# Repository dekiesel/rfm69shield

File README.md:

# rfm69shield
# rfm69shield
TODO: The extra GND isn't connected to any GND line

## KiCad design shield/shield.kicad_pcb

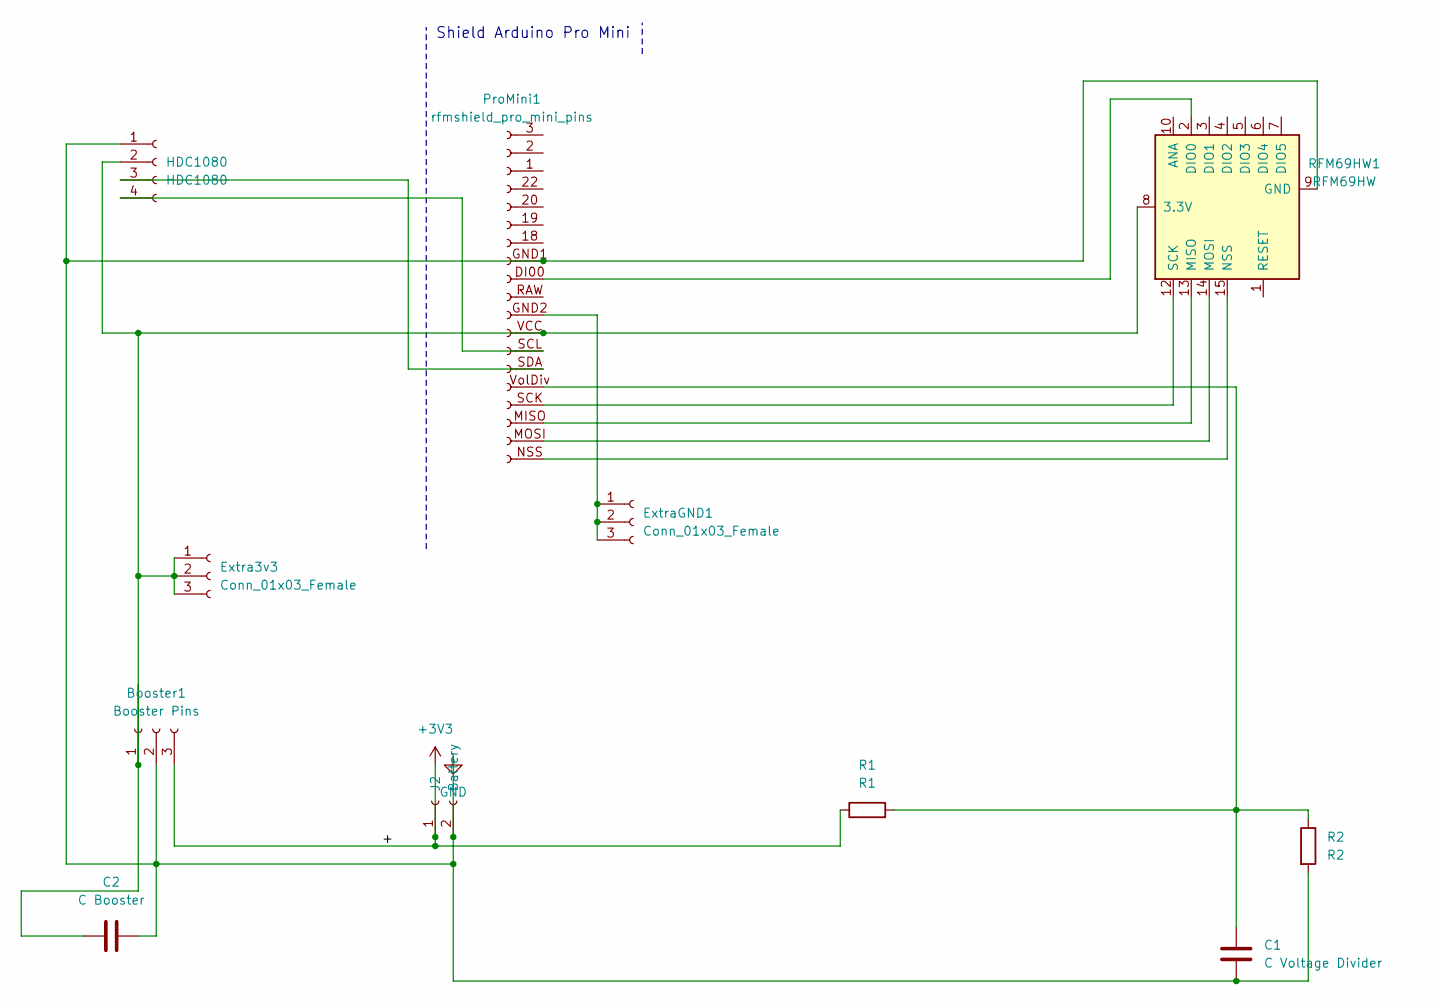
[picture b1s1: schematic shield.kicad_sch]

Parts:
Booster1: Booster Pins; PinHeader_1x03_P2.54mm_Vertical
C1: C Voltage Divider; CP_Radial_D6.3mm_P2.50mm
C2: C Booster; CP_Radial_D6.3mm_P2.50mm
Extra3v3: Conn_01x03_Female; PinHeader_1x03_P2.54mm_Vertical
ExtraGND1: Conn_01x03_Female; PinHeader_1x03_P2.54mm_Vertical
HDC1080: HDC1080; PinHeader_1x04_P2.54mm_Vertical
J2: Battery; PinHeader_1x02_P2.54mm_Vertical
ProMini1: rfmshield_pro_mini_pins; pro_mini_rfmshield
R1: R1; R_Axial_DIN0207_L6.3mm_D2.5mm_P10.16mm_Horizontal
R2: R2; R_Axial_DIN0207_L6.3mm_D2.5mm_P10.16mm_Horizontal
RFM69HW1: RFM69HW; HOPERF_RFM69HW

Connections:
+3V3: Booster1.3, J2.1, R1.1
GND: Booster1.2, C1.2, C2.2, HDC1080.1, J2.2, ProMini1.GND1, R2.2, RFM69HW1.9 (GND), RFM69HW1.11 (GND)
unnamed: Booster1.1, C2.1, Extra3v3.1, Extra3v3.2, Extra3v3.3, HDC1080.2, ProMini1.VCC, RFM69HW1.8 (3.3V)
unnamed: C1.1, ProMini1.VolDiv, R1.2, R2.1
unnamed: ExtraGND1.1, ExtraGND1.2, ExtraGND1.3, ProMini1.GND2
unnamed: HDC1080.3, ProMini1.SDA
unnamed: HDC1080.4, ProMini1.SCL
unnamed: ProMini1.DI00, RFM69HW1.2 (DIO0)
unnamed: ProMini1.MISO, RFM69HW1.13 (MISO)
unnamed: ProMini1.MOSI, RFM69HW1.14 (MOSI)
unnamed: ProMini1.NSS, RFM69HW1.15 (NSS)
unnamed: ProMini1.SCK, RFM69HW1.12 (SCK)

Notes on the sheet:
Shield Arduino Pro Mini

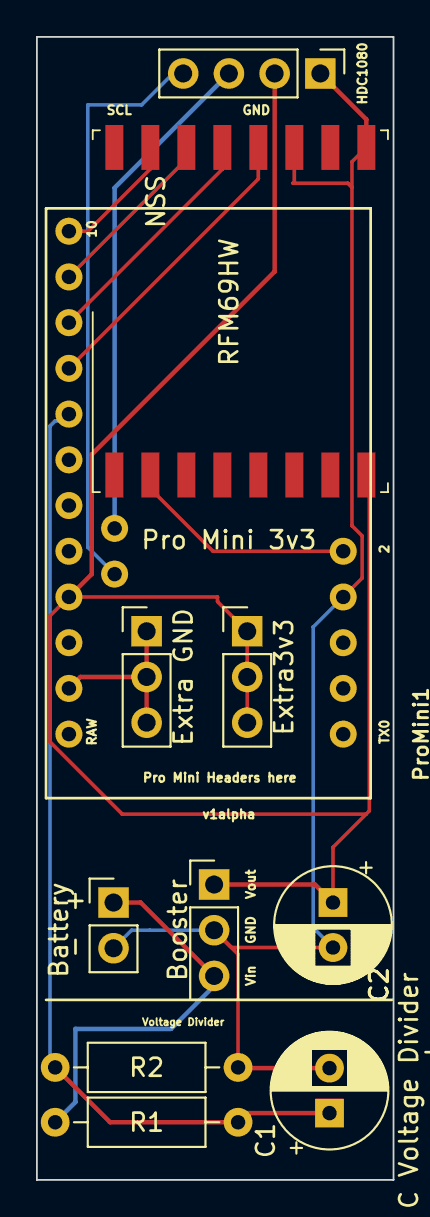
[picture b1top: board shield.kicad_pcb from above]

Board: 2 copper layers, 19.8 x 63.5 mm, 11 parts (0 on the bottom side), 12 nets.

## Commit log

2022-07-13 initial com
2022-07-15 pre holiday commit
2022-07-18 v1-pre renice
2022-08-02 moved tag
2022-08-02 pics
2022-08-02 gerber
2022-08-02 connected Vout
2022-08-04 final changes before printing
2022-08-08 version v1alpha, sent to jclpcb
2022-08-09 pics2
2022-08-09 tht issue
2024-09-24 cleanup
2024-09-24 alpha2
2024-09-24 alpha2 ready
2024-09-24 pngs
2024-09-24 gerbers
2024-09-24 drillfiles
2024-09-24 drill2
